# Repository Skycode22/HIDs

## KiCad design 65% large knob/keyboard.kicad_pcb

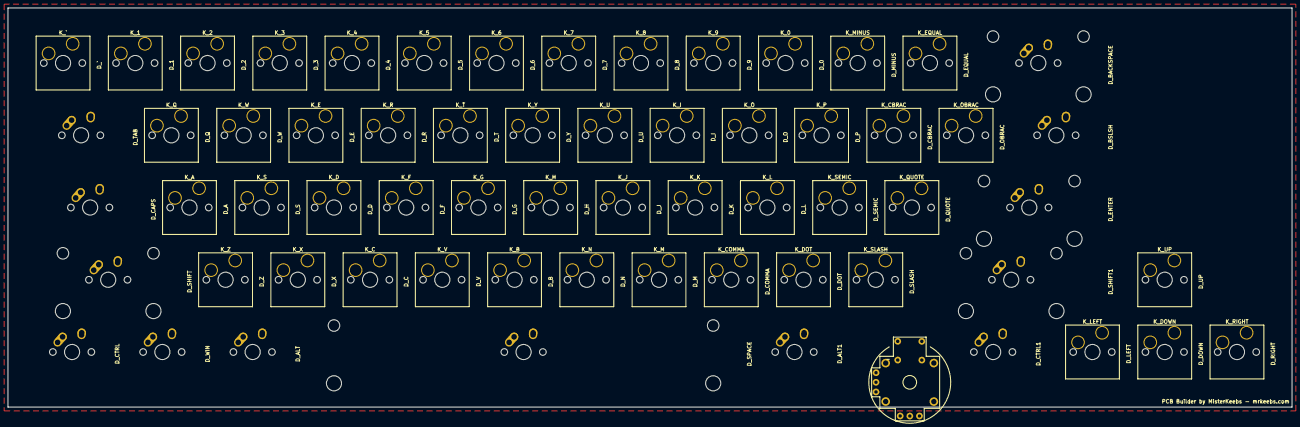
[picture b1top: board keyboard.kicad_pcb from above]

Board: 2 copper layers, 338.6 x 105.2 mm, 126 parts (0 on the bottom side), 16 nets, no tracks yet.

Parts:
D_0, D_1, D_2, D_3, D_4, D_5, D_6, D_7, D_8, D_9: D; nothing
D_A: D; nothing
D_ALT, D_ALT1: D; nothing
D_B: D; nothing
D_BACKSPACE: D; nothing
D_BSLSH: D; nothing
D_C: D; nothing
D_CAPS: D; nothing
D_CBRAC: D; nothing
D_COMMA: D; nothing
D_CTRL, D_CTRL1: D; nothing
D_D: D; nothing
D_DOT: D; nothing
D_DOWN: D; nothing
D_E: D; nothing
D_ENTER: D; nothing
D_EQUAL: D; nothing
D_F: D; nothing
D_G: D; nothing
D_H: D; nothing
D_I: D; nothing
D_J: D; nothing
D_K: D; nothing
D_L: D; nothing
D_LEFT: D; nothing
D_M: D; nothing
D_MINUS: D; nothing
D_N: D; nothing
D_O: D; nothing
D_OBRAC: D; nothing
D_P: D; nothing
D_Q: D; nothing
D_QUOTE: D; nothing
D_R: D; nothing
D_RIGHT: D; nothing
D_S: D; nothing
D_SEMIC: D; nothing
D_SHIFT, D_SHIFT1: D; nothing
D_SLASH: D; nothing
D_SPACE: D; nothing
D_T: D; nothing
D_TAB: D; nothing
D_U: D; nothing
D_UP: D; nothing
D_V: D; nothing
D_W: D; nothing
D_WIN: D; nothing
D_X: D; nothing
D_Y: D; nothing
D_Z: D; nothing
D_`: D; nothing
K_0, K_1, K_2, K_3, K_4, K_5, K_6, K_7, K_8, K_9: KEYSW; SW_Hotswap_Kailh_MX_Plated_1.00u
K_A: KEYSW; SW_Hotswap_Kailh_MX_Plated_1.00u
K_ALT, K_ALT1: KEYSW; MX-1.25U-NoLED
K_B: KEYSW; SW_Hotswap_Kailh_MX_Plated_1.00u
K_BACKSPACE: KEYSW; MX-2U-NoLED
K_BSLSH: KEYSW; MX-1.5U-NoLED
K_C: KEYSW; SW_Hotswap_Kailh_MX_Plated_1.00u
K_CAPS: KEYSW; MX-1.75U-NoLED
K_CBRAC: KEYSW; SW_Hotswap_Kailh_MX_Plated_1.00u
K_COMMA: KEYSW; SW_Hotswap_Kailh_MX_Plated_1.00u
K_CTRL, K_CTRL1: KEYSW; MX-1.25U-NoLED
K_D: KEYSW; SW_Hotswap_Kailh_MX_Plated_1.00u
K_DOT: KEYSW; SW_Hotswap_Kailh_MX_Plated_1.00u
K_DOWN: KEYSW; SW_Hotswap_Kailh_MX_Plated_1.00u
K_E: KEYSW; SW_Hotswap_Kailh_MX_Plated_1.00u
K_ENTER: KEYSW; MX-2.25U-NoLED
K_EQUAL: KEYSW; SW_Hotswap_Kailh_MX_Plated_1.00u
K_F: KEYSW; SW_Hotswap_Kailh_MX_Plated_1.00u
K_G: KEYSW; SW_Hotswap_Kailh_MX_Plated_1.00u
K_H: KEYSW; SW_Hotswap_Kailh_MX_Plated_1.00u
K_I: KEYSW; SW_Hotswap_Kailh_MX_Plated_1.00u
K_J: KEYSW; SW_Hotswap_Kailh_MX_Plated_1.00u
K_K: KEYSW; SW_Hotswap_Kailh_MX_Plated_1.00u
K_L: KEYSW; SW_Hotswap_Kailh_MX_Plated_1.00u
K_LEFT: KEYSW; SW_Hotswap_Kailh_MX_Plated_1.00u
K_M: KEYSW; SW_Hotswap_Kailh_MX_Plated_1.00u
K_MINUS: KEYSW; SW_Hotswap_Kailh_MX_Plated_1.00u
K_N: KEYSW; SW_Hotswap_Kailh_MX_Plated_1.00u
K_O: KEYSW; SW_Hotswap_Kailh_MX_Plated_1.00u
K_OBRAC: KEYSW; SW_Hotswap_Kailh_MX_Plated_1.00u
K_P: KEYSW; SW_Hotswap_Kailh_MX_Plated_1.00u
K_Q: KEYSW; SW_Hotswap_Kailh_MX_Plated_1.00u
K_QUOTE: KEYSW; SW_Hotswap_Kailh_MX_Plated_1.00u
K_R: KEYSW; SW_Hotswap_Kailh_MX_Plated_1.00u
K_RIGHT: KEYSW; SW_Hotswap_Kailh_MX_Plated_1.00u
K_S: KEYSW; SW_Hotswap_Kailh_MX_Plated_1.00u
K_SEMIC: KEYSW; SW_Hotswap_Kailh_MX_Plated_1.00u
K_SHIFT: KEYSW; MX-2.25U-NoLED
K_SHIFT1: KEYSW; MX-2.75U-NoLED
K_SLASH: KEYSW; SW_Hotswap_Kailh_MX_Plated_1.00u
K_SPACE: KEYSW; MX-6.25U-NoLED
K_T: KEYSW; SW_Hotswap_Kailh_MX_Plated_1.00u
K_TAB: KEYSW; MX-1.5U-NoLED
K_U: KEYSW; SW_Hotswap_Kailh_MX_Plated_1.00u
K_UP: KEYSW; SW_Hotswap_Kailh_MX_Plated_1.00u
K_V: KEYSW; SW_Hotswap_Kailh_MX_Plated_1.00u
K_W: KEYSW; SW_Hotswap_Kailh_MX_Plated_1.00u
K_WIN: KEYSW; MX-1.25U-NoLED
K_X: KEYSW; SW_Hotswap_Kailh_MX_Plated_1.00u
K_Y: KEYSW; SW_Hotswap_Kailh_MX_Plated_1.00u
K_Z: KEYSW; SW_Hotswap_Kailh_MX_Plated_1.00u
K_`: KEYSW; SW_Hotswap_Kailh_MX_Plated_1.00u

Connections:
/col0: K_CAPS.1, K_CTRL.1, K_TAB.1, K_`.1
/col1: K_1.1, K_SHIFT.1, K_WIN.1
/col2: K_2.1, K_A.1, K_Q.1, K_Z.1
/col3: K_3.1, K_ALT.1, K_S.1, K_W.1, K_X.1
/col4: K_4.1, K_C.1, K_D.1, K_E.1
/col5: K_5.1, K_F.1, K_R.1, K_V.1
/col6: K_6.1, K_B.1, K_G.1, K_SPACE.1, K_T.1
/col7: K_7.1, K_H.1, K_N.1, K_Y.1
/col8: K_8.1, K_J.1, K_M.1, K_U.1
/col9: K_9.1, K_COMMA.1, K_I.1, K_K.1
/col10: K_0.1, K_ALT1.1, K_DOT.1, K_L.1, K_O.1
/col11: K_MINUS.1, K_P.1, K_SEMIC.1, K_SLASH.1
/col12: K_CBRAC.1, K_EQUAL.1, K_QUOTE.1
/col13: K_CTRL1.1, K_ENTER.1, K_OBRAC.1, K_SHIFT1.1
/col14: K_BACKSPACE.1, K_BSLSH.1, K_LEFT.1
/col15: K_DOWN.1, K_UP.1

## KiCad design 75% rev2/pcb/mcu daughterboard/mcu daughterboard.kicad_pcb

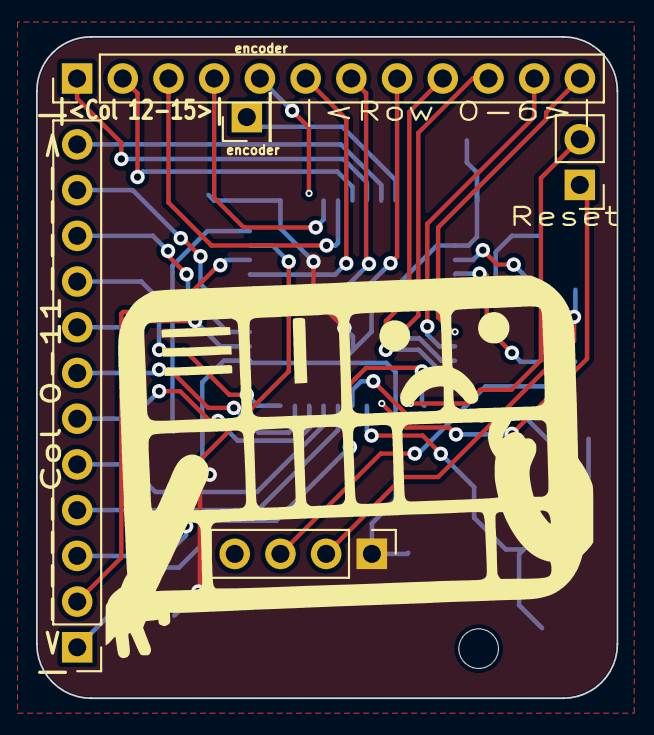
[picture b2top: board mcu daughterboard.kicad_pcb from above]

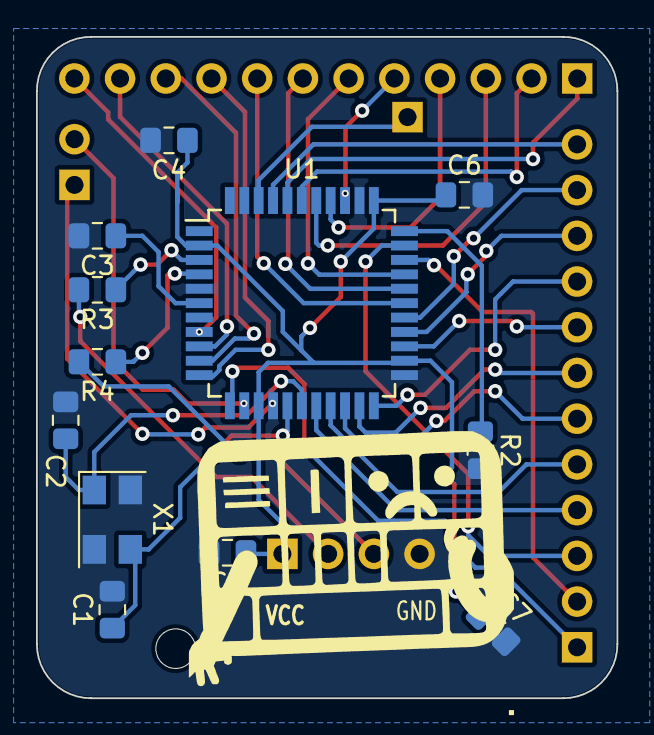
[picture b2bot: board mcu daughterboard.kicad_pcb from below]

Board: 2 copper layers, 32.2 x 36.7 mm, 17 parts (12 on the bottom side), 35 nets.

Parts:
*: '; PinHeader_1x04_P2.54mm_Vertical
*#2: '; PinHeader_1x01_P2.54mm_Vertical
*#3: PinHeader_1x02_P2.54mm_Vertical
*#4: 1; PinHeader_1x12_P2.54mm_Vertical
*#5: '; PinHeader_1x12_P2.54mm_Vertical
C1, C2, C3, C4, C5, C6, C7: 22pF; C_0805_2012Metric_Pad1.15x1.40mm_HandSolder
R2: 10k; R_0805_2012Metric_Pad1.15x1.40mm_HandSolder
R3, R4: 22; R_0805_2012Metric_Pad1.15x1.40mm_HandSolder
U1: ATMEGA32U4; TQFP-44_10x10mm_P0.8mm
X1: XTAL_GND; Crystal_SMD_5032-4Pin_5.0x3.2mm

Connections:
/col0: *#5.1, U1.12
/col1: *#5.2, U1.31
/col2: *#5.3, U1.32
/col3: *#5.4, U1.18
/col4: *#5.5, U1.19
/col5: *#5.6, U1.20
/col6: *#5.7, U1.21
/col7: *#5.8, U1.25
/col8: *#5.9, U1.22
/col9: *#5.10, U1.26
/col10: *#5.11, U1.27
/col11: *#5.12, U1.41
/col12: *#4.1, U1.40
/col13: *#4.2, U1.39
/col14: *#4.3, U1.38
/col15: *#4.4, U1.37
/row0: *#4.12, U1.8
/row1: *#4.11, U1.9
/row2: *#4.10, U1.10
/row3: *#4.9, U1.11
/row4: *#4.8, U1.28
/row5: *#4.7, U1.29
/row6: *#4.6, U1.30
GND: *.4, C1.2, C2.2, C3.2, C4.2, C5.2, C6.2, C7.2, R2.2, U1.5, U1.15, U1.23, U1.35, U1.43, X1.2, X1.4
unnamed: C1.1, U1.16, X1.1
unnamed: C2.1, U1.17, X1.3
unnamed: C3.1, U1.6
unnamed: R2.1, U1.33
unnamed: R3.1, U1.3
unnamed: R4.1, U1.4
unnamed: *#2.1, U1.42
unnamed: *#4.5, U1.36
unnamed: *.2, R3.2
unnamed: *.3, R4.2
VCC: *.1, C4.1, C5.1, C6.1, C7.1, U1.2, U1.14, U1.24, U1.34
